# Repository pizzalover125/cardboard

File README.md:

# cardboard
a credit-card-sized split keyboard. world's smallest split keyboard.

## Images

## BOM
* 2x Seeed Studio XIAO RP2040 ($11.99 from Seeed Studio)
* 2x TRRS Sockets + 1x TRRS Cable + 100x Diodes + 100x Resistors ($14.98 from Keeb.io)
* 100x 6mm Pushbuttons ($3.57 from Amazon)
* 5x PCB ($7.30 from JLC)
* 2x IO Expander (FREE from cardpad)
* 8x Neopixels (FREE from hackpad)
**Total: $37.84**

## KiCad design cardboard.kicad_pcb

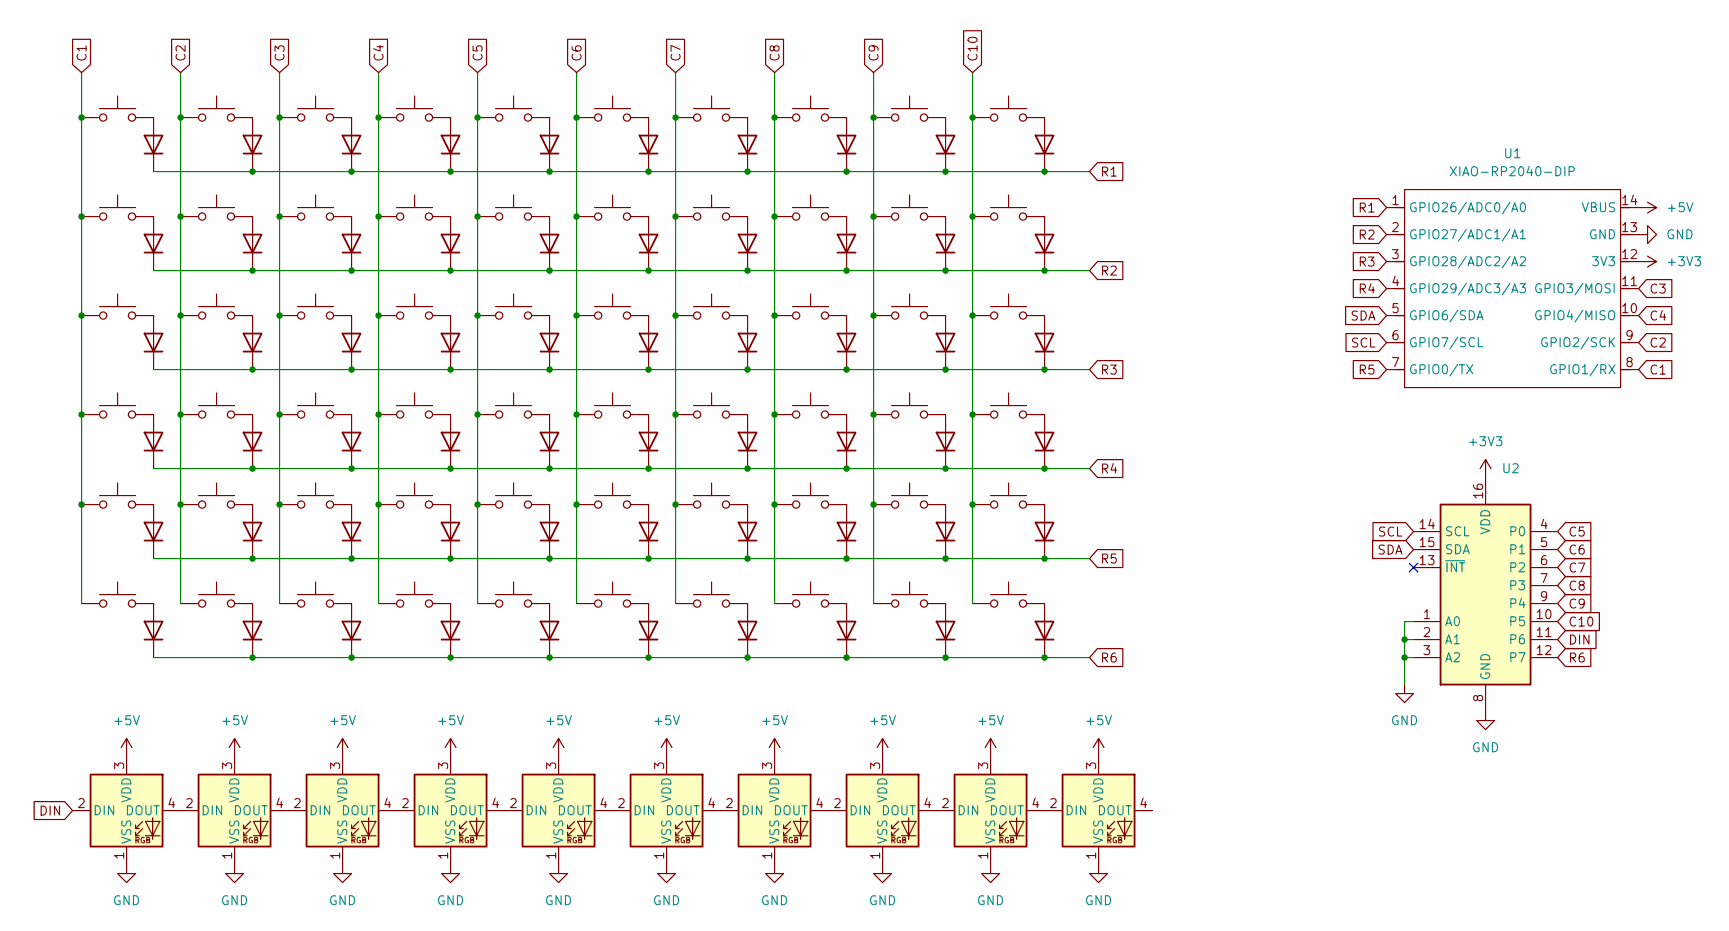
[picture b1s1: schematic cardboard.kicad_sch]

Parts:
D1, D2, D3, D4, D5, D6, D7, D8, D9, D10, D11, D12, D13, D14, D15, D16, D17, D18, D19, D20, D21, D22, D23, D24, D25, D26, D27, D28, D29, D30, D31, D32, D33, D34, D35, D36, D37, D38, D39, D40, D41, D42, D43, D44, D45, D46, D47, D48, D49, D50, D61, D62, D63, D64, D65, D66, D67, D68, D69, D70: D; D_0402_1005Metric
D51, D52, D53, D54, D55, D56, D57, D58, D59, D60: SK6812; LED_SK6812_PLCC4_5.0x5.0mm_P3.2mm
SW1, SW2, SW3, SW4, SW5, SW6, SW7, SW8, SW9, SW10, SW11, SW12, SW13, SW14, SW15, SW16, SW17, SW18, SW19, SW20, SW21, SW22, SW23, SW24, SW25, SW26, SW27, SW28, SW29, SW30, SW31, SW32, SW33, SW34, SW35, SW36, SW37, SW38, SW39, SW40, SW41, SW42, SW43, SW44, SW45, SW46, SW47, SW48, SW49, SW50, SW51, SW52, SW53, SW54, SW55, SW56, SW57, SW58, SW59, SW60: SW_Push; SW_B3U-1000P
U1: XIAO-RP2040-DIP
U2: PCF8574AP; DIP-16_W7.62mm

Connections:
+3V3: U1.12 (3V3), U2.16 (VDD)
+5V: D51.3 (VDD), D52.3 (VDD), D53.3 (VDD), D54.3 (VDD), D55.3 (VDD), D56.3 (VDD), D57.3 (VDD), D58.3 (VDD), D59.3 (VDD), D60.3 (VDD), U1.14 (VBUS)
C1: SW1.1, SW2.1, SW3.1, SW4.1, SW5.1, SW51.1, U1.8 (GPIO1/RX)
C2: SW6.1, SW7.1, SW8.1, SW9.1, SW10.1, SW52.1, U1.9 (GPIO2/SCK)
C3: SW11.1, SW12.1, SW13.1, SW14.1, SW15.1, SW53.1, U1.11 (GPIO3/MOSI)
C4: SW16.1, SW17.1, SW18.1, SW19.1, SW20.1, SW54.1, U1.10 (GPIO4/MISO)
C5: SW21.1, SW22.1, SW23.1, SW24.1, SW25.1, SW55.1, U2.4 (P0)
C6: SW26.1, SW27.1, SW28.1, SW29.1, SW30.1, SW56.1, U2.5 (P1)
C7: SW31.1, SW32.1, SW33.1, SW34.1, SW35.1, SW57.1, U2.6 (P2)
C8: SW36.1, SW37.1, SW38.1, SW39.1, SW40.1, SW58.1, U2.7 (P3)
C9: SW41.1, SW42.1, SW43.1, SW44.1, SW45.1, SW59.1, U2.9 (P4)
C10: SW46.1, SW47.1, SW48.1, SW49.1, SW50.1, SW60.1, U2.10 (P5)
DIN: D51.2 (DIN), U2.11 (P6)
GND: D51.1 (VSS), D52.1 (VSS), D53.1 (VSS), D54.1 (VSS), D55.1 (VSS), D56.1 (VSS), D57.1 (VSS), D58.1 (VSS), D59.1 (VSS), D60.1 (VSS), U1.13 (GND), U2.1 (A0), U2.2 (A1), U2.3 (A2), U2.8 (GND)
unnamed: D1.2 (A), SW1.2
unnamed: D2.2 (A), SW2.2
unnamed: D3.2 (A), SW3.2
unnamed: D4.2 (A), SW4.2
unnamed: D5.2 (A), SW5.2
unnamed: D6.2 (A), SW6.2
unnamed: D7.2 (A), SW7.2
unnamed: D8.2 (A), SW8.2
unnamed: D9.2 (A), SW9.2
unnamed: D10.2 (A), SW10.2
unnamed: D11.2 (A), SW11.2
unnamed: D12.2 (A), SW12.2
unnamed: D13.2 (A), SW13.2
unnamed: D14.2 (A), SW14.2
unnamed: D15.2 (A), SW15.2
unnamed: D16.2 (A), SW16.2
unnamed: D17.2 (A), SW17.2
unnamed: D18.2 (A), SW18.2
unnamed: D19.2 (A), SW19.2
unnamed: D20.2 (A), SW20.2
unnamed: D21.2 (A), SW21.2
unnamed: D22.2 (A), SW22.2
unnamed: D23.2 (A), SW23.2
unnamed: D24.2 (A), SW24.2
unnamed: D25.2 (A), SW25.2
unnamed: D26.2 (A), SW26.2
unnamed: D27.2 (A), SW27.2
unnamed: D28.2 (A), SW28.2
unnamed: D29.2 (A), SW29.2
unnamed: D30.2 (A), SW30.2
unnamed: D31.2 (A), SW31.2
unnamed: D32.2 (A), SW32.2
unnamed: D33.2 (A), SW33.2
unnamed: D34.2 (A), SW34.2
unnamed: D35.2 (A), SW35.2
unnamed: D36.2 (A), SW36.2
unnamed: D37.2 (A), SW37.2
unnamed: D38.2 (A), SW38.2
unnamed: D39.2 (A), SW39.2
unnamed: D40.2 (A), SW40.2
unnamed: D41.2 (A), SW41.2
unnamed: D42.2 (A), SW42.2
unnamed: D43.2 (A), SW43.2
unnamed: D44.2 (A), SW44.2
unnamed: D45.2 (A), SW45.2
unnamed: D46.2 (A), SW46.2
unnamed: D47.2 (A), SW47.2
unnamed: D48.2 (A), SW48.2
unnamed: D49.2 (A), SW49.2
unnamed: D50.2 (A), SW50.2
unnamed: D51.4 (DOUT), D52.2 (DIN)
unnamed: D52.4 (DOUT), D53.2 (DIN)
unnamed: D53.4 (DOUT), D54.2 (DIN)
unnamed: D54.4 (DOUT), D55.2 (DIN)
unnamed: D55.4 (DOUT), D56.2 (DIN)
unnamed: D56.4 (DOUT), D57.2 (DIN)
unnamed: D57.4 (DOUT), D58.2 (DIN)
unnamed: D58.4 (DOUT), D59.2 (DIN)
unnamed: D59.4 (DOUT), D60.2 (DIN)
unnamed: D61.2 (A), SW51.2
unnamed: D62.2 (A), SW52.2
unnamed: D63.2 (A), SW53.2
unnamed: D64.2 (A), SW54.2
unnamed: D65.2 (A), SW55.2
unnamed: D66.2 (A), SW56.2
unnamed: D67.2 (A), SW57.2
unnamed: D68.2 (A), SW58.2
unnamed: D69.2 (A), SW59.2
unnamed: D70.2 (A), SW60.2
R1: D1.1 (K), D6.1 (K), D11.1 (K), D16.1 (K), D21.1 (K), D26.1 (K), D31.1 (K), D36.1 (K), D41.1 (K), D46.1 (K), U1.1 (GPIO26/ADC0/A0)
R2: D2.1 (K), D7.1 (K), D12.1 (K), D17.1 (K), D22.1 (K), D27.1 (K), D32.1 (K), D37.1 (K), D42.1 (K), D47.1 (K), U1.2 (GPIO27/ADC1/A1)
R3: D3.1 (K), D8.1 (K), D13.1 (K), D18.1 (K), D23.1 (K), D28.1 (K), D33.1 (K), D38.1 (K), D43.1 (K), D48.1 (K), U1.3 (GPIO28/ADC2/A2)
R4: D4.1 (K), D9.1 (K), D14.1 (K), D19.1 (K), D24.1 (K), D29.1 (K), D34.1 (K), D39.1 (K), D44.1 (K), D49.1 (K), U1.4 (GPIO29/ADC3/A3)
R5: D5.1 (K), D10.1 (K), D15.1 (K), D20.1 (K), D25.1 (K), D30.1 (K), D35.1 (K), D40.1 (K), D45.1 (K), D50.1 (K), U1.7 (GPIO0/TX)
R6: D61.1 (K), D62.1 (K), D63.1 (K), D64.1 (K), D65.1 (K), D66.1 (K), D67.1 (K), D68.1 (K), D69.1 (K), D70.1 (K), U2.12 (P7)
SCL: U1.6 (GPIO7/SCL), U2.14 (SCL)
SDA: U1.5 (GPIO6/SDA), U2.15 (SDA)

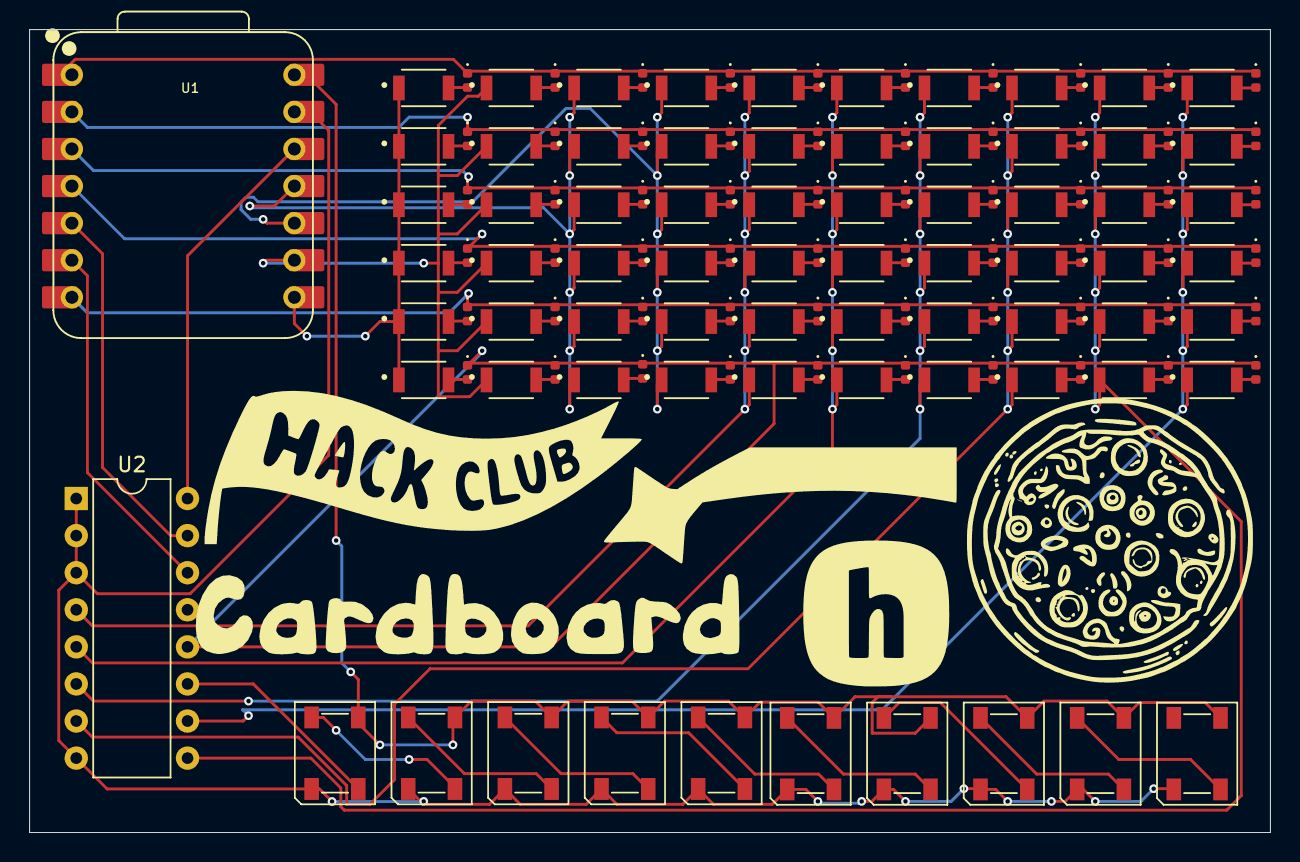
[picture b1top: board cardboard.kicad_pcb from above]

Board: 2 copper layers, 85.0 x 55.0 mm, 132 parts (0 on the bottom side), 91 nets.

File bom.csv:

Designator,Footprint,Quantity,Value,LCSC Part #
"D1, D10, D11, D12, D13, D14, D15, D16, D17, D18, D19, D2, D20, D21, D22, D23, D24, D25, D26, D27, D28, D29, D3, D30, D31, D32, D33, D34, D35, D36, D37, D38, D39, D4, D40, D41, D42, D43, D44, D45, D46, D47, D48, D49, D5, D50, D6, D61, D62, D63, D64, D65, D66, D67, D68, D69, D7, D70, D8, D9",0402,60,D,
"D51, D52, D53, D54, D55, D56, D57, D58, D59, D60",LED_SK6812_PLCC4_5.0x5.0mm_P3.2mm,10,SK6812,
"SW1, SW10, SW11, SW12, SW13, SW14, SW15, SW16, SW17, SW18, SW19, SW2, SW20, SW21, SW22, SW23, SW24, SW25, SW26, SW27, SW28, SW29, SW3, SW30, SW31, SW32, SW33, SW34, SW35, SW36, SW37, SW38, SW39, SW4, SW40, SW41, SW42, SW43, SW44, SW45, SW46, SW47, SW48, SW49, SW5, SW50, SW51, SW52, SW53, SW54, SW55, SW56, SW57, SW58, SW59, SW6, SW60, SW7, SW8, SW9",SW_B3U-1000P,60,SW_Push,
U1,XIAO-RP2040-DIP,1,XIAO-RP2040-DIP,
U2,DIP-16_W7.62mm,1,PCF8574AP,
